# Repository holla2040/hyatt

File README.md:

# hyatt
A CNC wood router based on OpenBuilds WorkBee 1010, [Cypress PSoC 5LP CY8CKIT-059](http://www.cypress.com/documentation/development-kitsboards/cy8ckit-059-psoc-5lp-prototyping-kit-onboard-programmer-and) and [PSoC GRBL](https://github.com/bdring/Grbl_USB_Native). 

Hyatt Feature Set
* CY8KIT-059 based design
* 4 axis CNC controller, Dring GRBL port - PSoC HW pulse generation, debounce, interrupts
* Spindle speed/direction control - PSoC PWM
* Piezo element work piece probe - PSoC opamp, ADC, DAC comparator, interrupt
* Motor drive current monitor - PSoC analog mux and ADC
* Supply voltage monitor - PSoC ADC
* WiFi link with webserver, OTA, flash filesystem, websockets, TCP-serial bridge using ESP8266 - PSoC USART

Operator Interface
* 12 illuminated buttons via I2C I/O port expanders - PSoC I2C Fixed master
* Jog wheel with quad encoder - PSoC quad decoder
* 20x4 LCD panel display - PSoC I2C Fixed master
* 3.5" TFT 480x320 resistive touch screen display, attached to X axis gantry - PSoC USART
* Real-time feed speed override - PSoC ADC
* SDCard reader- PSoC SPI EmFile library
* Wireless CNC pendant - DirecTV remote control - my custom IR decoder using PSoC digital logic

[Hyatt Openbeam Workbee 1010 Settings](settings.txt)

PCB board, 100x100mm 2 layer, mixed through and smt parts

---

Getting boards from [JLCPCB](https://jlcpcb.com/), $2 for 10 boards + $18 DHL US shipping.

---

[Watch more hyatt videos](https://www.youtube.com/user/holla2040/search?query=hyatt)

---

Project named after Dale Hyatt, the one of the original K&F guitar amp cabinet makers. See "[The Sound Heard 'Round the World](https://www.halleonardbooks.com/product/viewproduct.action?itemid=332779 "Fender - The Sound Heard 'Round the World")", Richard Smith, p28.

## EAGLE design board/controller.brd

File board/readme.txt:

This information, board files, assembly instructions and bill of
materials are company confidental.
Not for distribution.

board
    hyatt

version
    1.0

date
    180804

fudicials at
    10,10
    96.88 

2 layer description
    2 layer board
        crc component cream
        plc component side silkscreen
        stc component side solder stop mask
        cmp component side copper
        sol solder side copper
        sts solder side solder stop mask
        pls solder side silkscreen
        crs solder cream

        drd drill data
        dri drill info
        gpi gerber info

2 layer stack up sequence
    top     x.cmp
    bottom  x.sol

contact info
    Craig Hollabaugh
    970 690 4911
    craig@hollabaugh.com

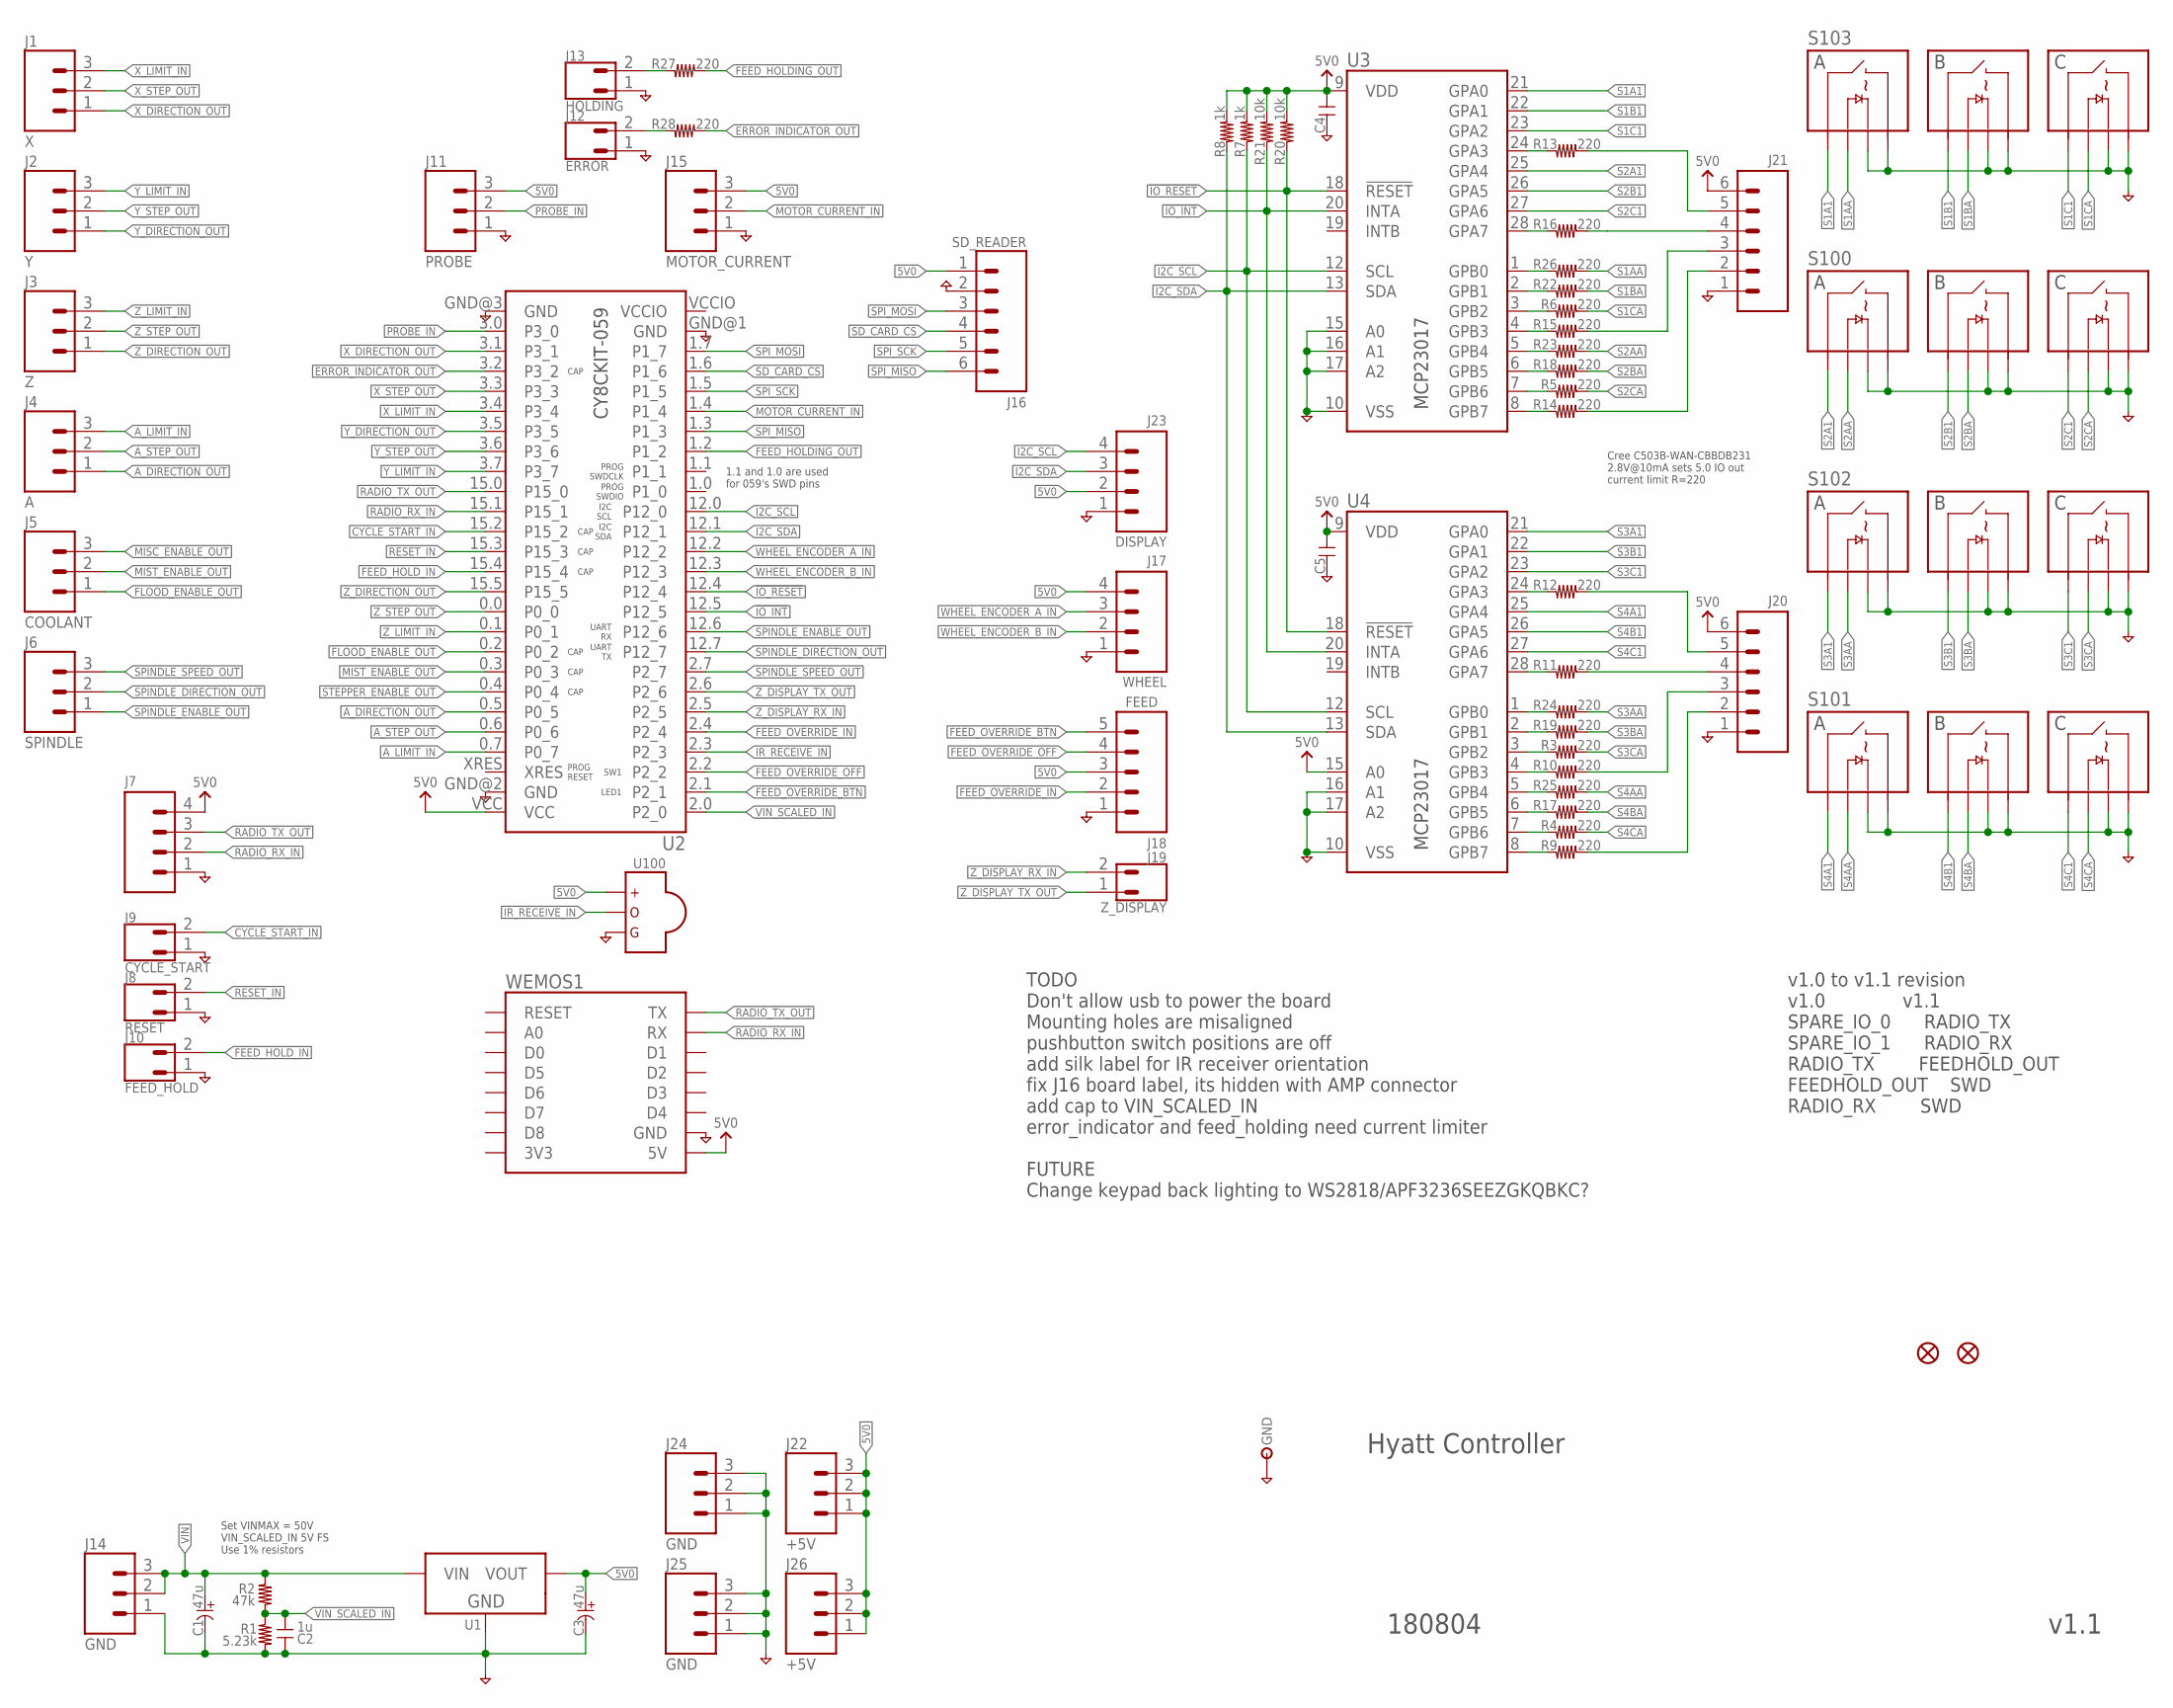
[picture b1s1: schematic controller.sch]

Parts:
C1, C3: 47u; E5-10
C2: 1u; C0603
C4, C5: C-0603; C0603
FID1, FID2: FIDUCIAL1.5X3; FIDUCIAL-1.5X3
GND: TESTPOINTTHRU; TPTHRU
J1: X; CONN-3.81MM-KF2EDG-3
J2: Y; CONN-3.81MM-KF2EDG-3
J3: Z; CONN-3.81MM-KF2EDG-3
J4: A; CONN-3.81MM-KF2EDG-3
J5: COOLANT; CONN-3.81MM-KF2EDG-3
J6: SPINDLE; CONN-3.81MM-KF2EDG-3
J7: CONN-04-0.1; 1X04
J8: RESET; CONN-.100-2
J9: CYCLE_START; CONN-.100-2
J10: FEED_HOLD; CONN-.100-2
J11: PROBE; CONN-3.81MM-KF2EDG-3
J12: ERROR; CONN-.100-2
J13: HOLDING; CONN-.100-2
J14, J24, J25: GND; CONN-3.81MM-KF2EDG-3
J15: MOTOR_CURRENT; CONN-3.81MM-KF2EDG-3
J16: SD_READER; 1X06
J17: WHEEL; CONN-.100-4
J18: FEED; 1X05
J19: Z_DISPLAY; CONN-3.81MM-KF2EDG-2
J20, J21: CONN-06-.100-VERT-HEADER; CONN-.100-6
J22, J26: +5V; CONN-3.81MM-KF2EDG-3
J23: DISPLAY; CONN-.100-4
R1: 5.23k; R0603
R2: 47k; R0603
R3, R4, R5, R6, R9, R10, R11, R12, R13, R14, R15, R16, R17, R18, R19, R22, R23, R24, R25, R26, R27, R28: 220; R0603
R7, R8: 1k; R0603
R20, R21: 10k; R0603
S100, S101, S102, S103: SWITCH-DTMF-3-LED
U1: VREG-SIP3
U2: BOARD-PSOC-CY8CKIT-059
U3, U4: MCP23017; SO28W
U100: SENSOR-IR-THRU; IRDETECTOR-THRU
WEMOS1: RADIO-WEMOS-D1-MINI; WEMOS-D1-MINI

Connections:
5V0: C3.+, C4.1, C5.1, J7.4, J11.3, J15.3, J16.1, J17.4, J18.3, J20.6, J21.6, J22.1, J22.2, J22.3, J23.2, J26.1, J26.2, J26.3, R7.2, R8.2, R20.2, R21.2, U1.3 (VOUT), U2.VCC, U3.9 (VDD), U4.9 (VDD), U4.15 (A0), U100.VCC, WEMOS1.5V
!IO_INT: R21.1, U2.12.5 (P12_5), U3.20 (INTA), U4.20 (INTA)
!IO_RESET: R20.1, U2.12.4 (P12_4), U3.18 (!RESET), U4.18 (!RESET)
A_DIRECTION_OUT: J4.1, U2.0.5 (P0_5)
A_LIMIT_IN: J4.3, U2.0.7 (P0_7)
A_STEP_OUT: J4.2, U2.0.6 (P0_6)
CYCLE_START_IN: J9.2, U2.15.2 (P15_2)
ERROR_INDICATOR_OUT: R28.2, U2.3.2 (P3_2)
FEED_HOLDING_OUT: R27.2, U2.1.2 (P1_2)
FEED_HOLD_IN: J10.2, U2.15.4 (P15_4)
FEED_OVERRIDE_BTN: J18.5, U2.2.1 (P2_1)
FEED_OVERRIDE_IN: J18.2, U2.2.4 (P2_4)
FEED_OVERRIDE_OFF: J18.4, U2.2.2 (P2_2)
FLOOD_ENABLE_OUT: J5.1, U2.0.2 (P0_2)
GND: C1.-, C2.2, C3.-, C4.2, C5.2, GND.1, J7.1, J8.1, J9.1, J10.1, J11.1, J12.1, J13.1, J14.1, J15.1, J16.2, J17.1, J18.1, J20.1, J21.1, J23.1, J24.1, J24.2, J24.3, J25.1, J25.2, J25.3, R1.1, S100.A_2, S100.A_C, S100.B_2, S100.B_C, S100.C_2, S100.C_C, S101.A_2, S101.A_C, S101.B_2, S101.B_C, S101.C_2, S101.C_C, S102.A_2, S102.A_C, S102.B_2, S102.B_C, S102.C_2, S102.C_C, S103.A_2, S103.A_C, S103.B_2, S103.B_C, S103.C_2, S103.C_C, U1.2 (GND), U2.GND@1 (GND), U2.GND@2 (GND), U2.GND@3 (GND), U3.10 (VSS), U3.15 (A0), U3.16 (A1), U3.17 (A2), U4.10 (VSS), U4.16 (A1), U4.17 (A2), U100.GND, WEMOS1.GND
I2C_SCL: J23.4, R7.1, U2.12.0 (P12_0), U3.12 (SCL), U4.12 (SCL)
I2C_SDA: J23.3, R8.1, U2.12.1 (P12_1), U3.13 (SDA), U4.13 (SDA)
IR_RECEIVE_IN: U2.2.3 (P2_3), U100.VOUT
MISC_ENABLE_OUT: J5.3
MIST_ENABLE_OUT: J5.2, U2.0.3 (P0_3)
MOTOR_CURRENT_IN: J15.2, U2.1.4 (P1_4)
unnamed: R26.1, U3.1 (GPB0)
unnamed: R22.1, U3.2 (GPB1)
unnamed: R13.1, U3.24 (GPA3)
unnamed: J21.5, R13.2
unnamed: R16.1, U3.28 (GPA7)
unnamed: J21.3, R15.2
unnamed: J21.4, R16.2
unnamed: R12.1, U4.24 (GPA3)
unnamed: R11.1, U4.28 (GPA7)
unnamed: J20.5, R12.2
unnamed: J20.4, R11.2
unnamed: J13.2, R27.1
unnamed: J12.2, R28.1
unnamed: R6.1, U3.3 (GPB2)
unnamed: R15.1, U3.4 (GPB3)
unnamed: R23.1, U3.5 (GPB4)
unnamed: R18.1, U3.6 (GPB5)
unnamed: R5.1, U3.7 (GPB6)
unnamed: R14.1, U3.8 (GPB7)
unnamed: R24.1, U4.1 (GPB0)
unnamed: R19.1, U4.2 (GPB1)
unnamed: R3.1, U4.3 (GPB2)
unnamed: R10.1, U4.4 (GPB3)
unnamed: R25.1, U4.5 (GPB4)
unnamed: R17.1, U4.6 (GPB5)
unnamed: R4.1, U4.7 (GPB6)
unnamed: R9.1, U4.8 (GPB7)
unnamed: J21.2, R14.2
unnamed: J20.3, R10.2
unnamed: J20.2, R9.2
PROBE_IN: J11.2, U2.3.0 (P3_0)
RADIO_RX_IN: J7.2, U2.15.1 (P15_1), WEMOS1.RX
RADIO_TX_OUT: J7.3, U2.15.0 (P15_0), WEMOS1.TX
RESET_IN: J8.2, U2.15.3 (P15_3)
S1A1: S103.A_1, U3.21 (GPA0)
S1AA: R26.2, S103.A_A
S1B1: S103.B_1, U3.22 (GPA1)
S1BA: R22.2, S103.B_A
S1C1: S103.C_1, U3.23 (GPA2)
S1CA: R6.2, S103.C_A
S2A1: S100.A_1, U3.25 (GPA4)
S2AA: R23.2, S100.A_A
S2B1: S100.B_1, U3.26 (GPA5)
S2BA: R18.2, S100.B_A
S2C1: S100.C_1, U3.27 (GPA6)
S2CA: R5.2, S100.C_A
S3A1: S102.A_1, U4.21 (GPA0)
S3AA: R24.2, S102.A_A
S3B1: S102.B_1, U4.22 (GPA1)
S3BA: R19.2, S102.B_A
S3C1: S102.C_1, U4.23 (GPA2)
S3CA: R3.2, S102.C_A
S4A1: S101.A_1, U4.25 (GPA4)
S4AA: R25.2, S101.A_A
S4B1: S101.B_1, U4.26 (GPA5)
S4BA: R17.2, S101.B_A
S4C1: S101.C_1, U4.27 (GPA6)
S4CA: R4.2, S101.C_A
SD_CARD_CS: J16.4, U2.1.6 (P1_6)
SPINDLE_DIRECTION_OUT: J6.2, U2.12.7 (P12_7)
SPINDLE_ENABLE_OUT: J6.1, U2.12.6 (P12_6)
SPINDLE_SPEED_OUT: J6.3, U2.2.7 (P2_7)
SPI_MISO: J16.6, U2.1.3 (P1_3)
SPI_MOSI: J16.3, U2.1.7 (P1_7)
SPI_SCK: J16.5, U2.1.5 (P1_5)
STEPPER_ENABLE_OUT: U2.0.4 (P0_4)
VIN: C1.+, J14.2, J14.3, R2.2, U1.1 (VIN)
VIN_SCALED_IN: C2.1, R1.2, R2.1, U2.2.0 (P2_0)
WHEEL_ENCODER_A_IN: J17.3, U2.12.2 (P12_2)
WHEEL_ENCODER_B_IN: J17.2, U2.12.3 (P12_3)
X_DIRECTION_OUT: J1.1, U2.3.1 (P3_1)
X_LIMIT_IN: J1.3, U2.3.4 (P3_4)
X_STEP_OUT: J1.2, U2.3.3 (P3_3)
Y_DIRECTION_OUT: J2.1, U2.3.5 (P3_5)
Y_LIMIT_IN: J2.3, U2.3.7 (P3_7)
Y_STEP_OUT: J2.2, U2.3.6 (P3_6)
Z_DIRECTION_OUT: J3.1, U2.15.5 (P15_5)
Z_DISPLAY_RX_IN: J19.2, U2.2.5 (P2_5)
Z_DISPLAY_TX_OUT: J19.1, U2.2.6 (P2_6)
Z_LIMIT_IN: J3.3, U2.0.1 (P0_1)
Z_STEP_OUT: J3.2, U2.0.0 (P0_0)

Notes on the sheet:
Hyatt Controller
180804
v1.1
TODO Don't allow usb to power the board Mounting holes are misaligned pushbutton switch positions are off add silk label for IR receiver orientation fix J16 board label, its hidden with AMP connector add cap to VIN_SCALED_IN error_indicator and feed_holding need current limiter FUTURE Change keypad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
Cree C503B-WAN-CBBDB231 2.8V@10mA sets 5.0 IO out current limit R=220
Set VINMAX = 50V VIN_SCALED_IN 5V FS Use 1% resistors
1.1 and 1.0 are used for 059's SWD pins
v1.0 to v1.1 revision v1.0 v1.1 SPARE_IO_0 RADIO_TX SPARE_IO_1 RADIO_RX RADIO_TX FEEDHOLD_OUT FEEDHOLD_OUT SWD RADIO_RX SWD

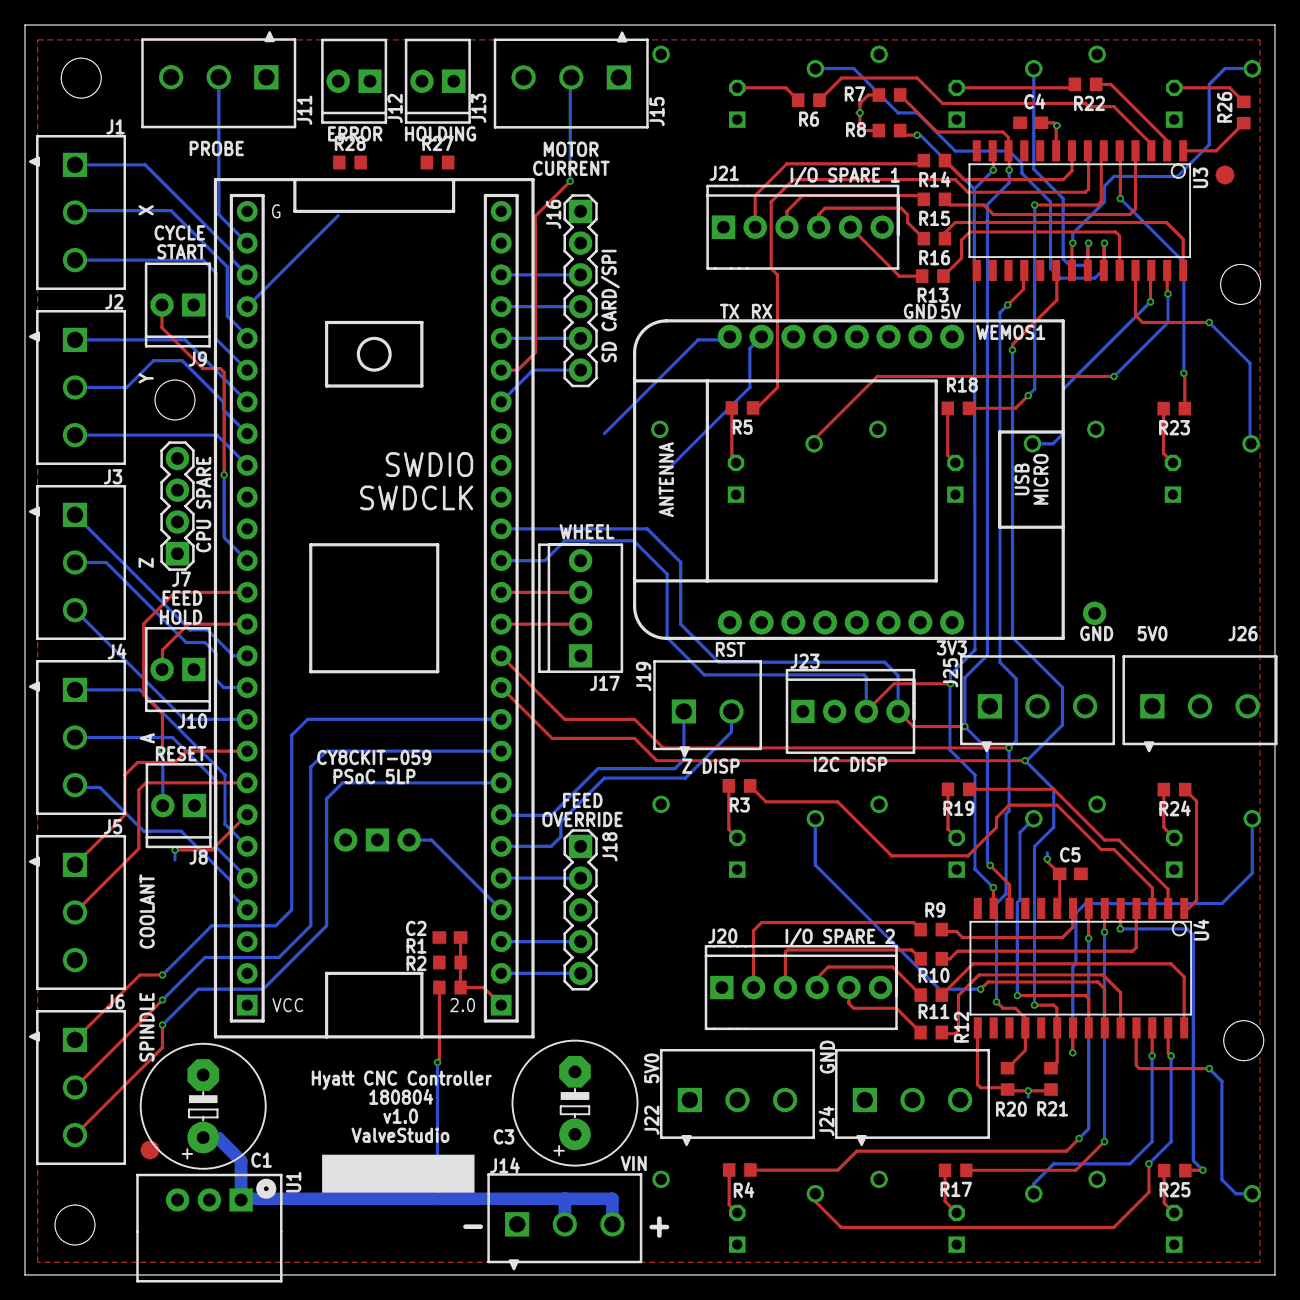
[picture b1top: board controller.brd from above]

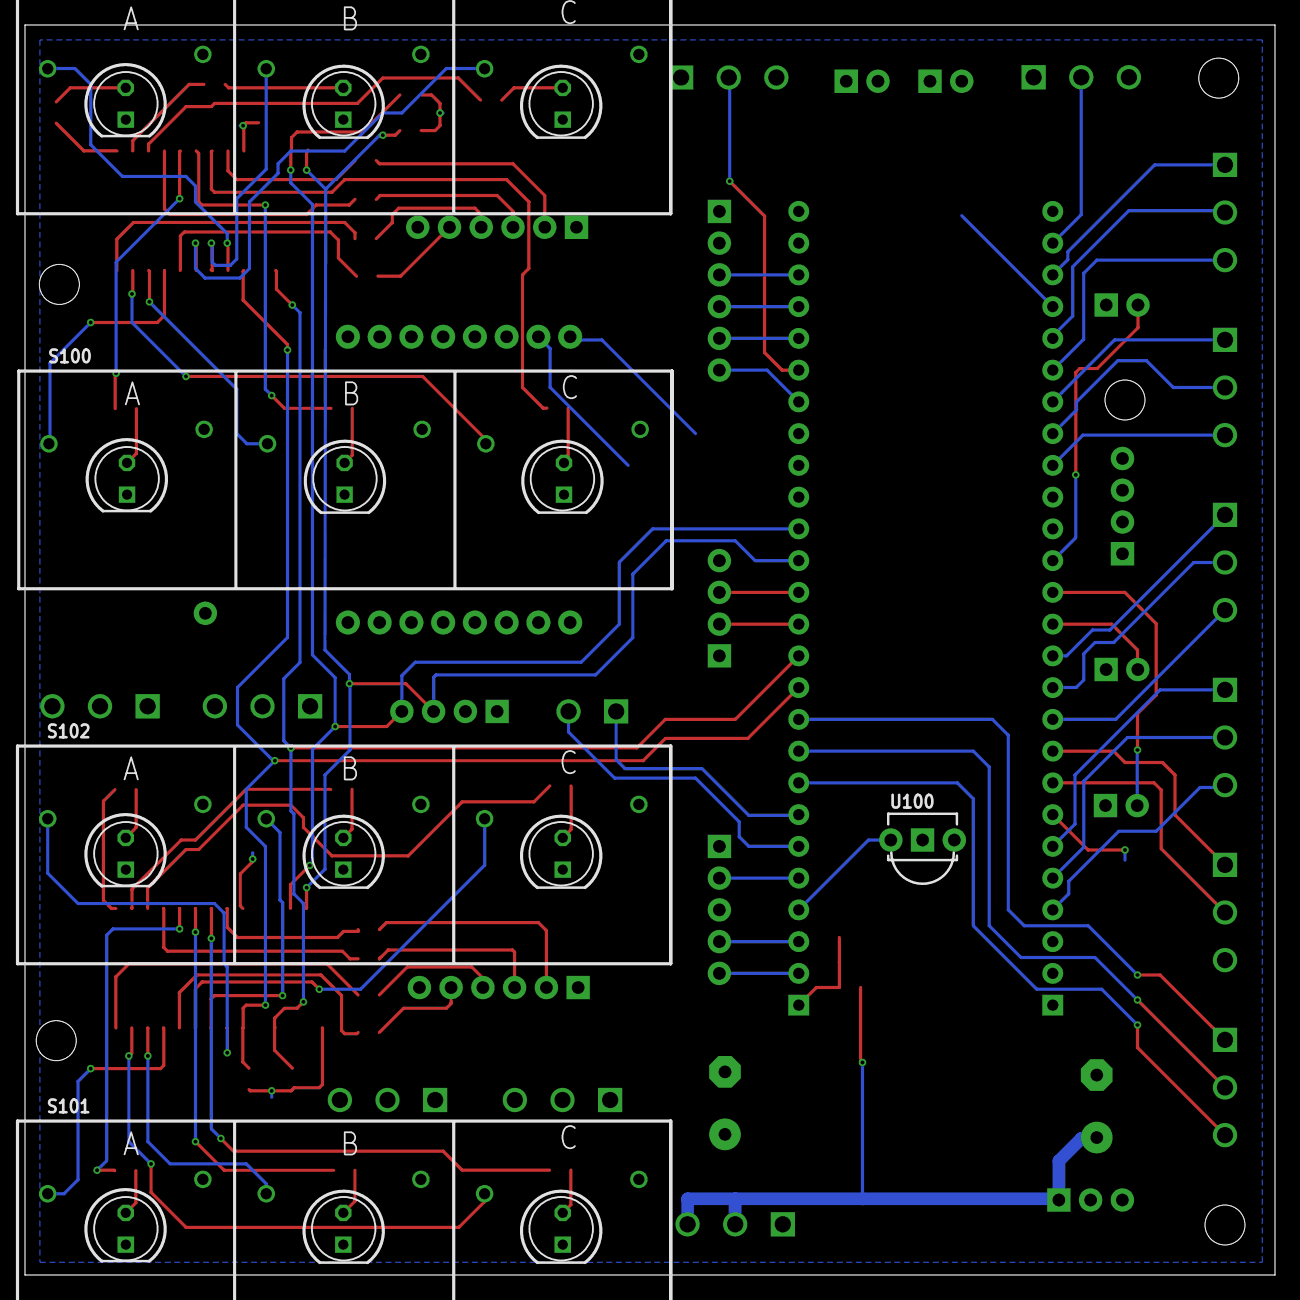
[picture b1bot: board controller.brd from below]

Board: 2 copper layers, 100.0 x 100.0 mm, 72 parts (5 on the bottom side), 100 nets.

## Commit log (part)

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2018-07-31 add dale hyatt image
2018-07-31 resized image
2018-07-31 fixing image
2018-07-31 readding dale hyatt
2018-07-31 initial add
2018-08-03 started routing added datasheets
2018-08-03 added datasheet continued routing
2018-08-03 pin assignment and routing near completion
2018-08-03 fixed 5V0/GND islands
2018-08-04 corrected keyboard switch dimensions
2018-08-04 initial add of files
2018-08-05 finished routing, almost ready to send
2018-08-06 re-organizing pin layout due to creator optimization
2018-08-06 reworked connector positions and pin mapping
2018-08-06 corrected wemos silkscreen
2018-08-06 fixed stepper_enable_out
2018-08-06 release v1.0
2018-08-06 removing readme with my name/phone
2018-08-06 initial add for design images
2018-08-06 corrected README lightened dale image
2018-08-07 initial add for board renders
2018-08-07 added workbee image
2018-08-08 fixed a couple issues and added creator's temp build files to ignore
2018-08-08 added 059 image
2018-08-08 update image
2018-08-17 updated wemos silk, added info to notes
2018-08-21 blinks 1A LED
2018-08-21 reading GPIOA, if S1A1 pressed, blinking pauses
2018-08-22 grouped the wires
2018-08-22 added component values to schematic cleaned up brd layout
2018-08-22 working on pushbutton interrupt
2018-08-24 now ignoring gerber files
2018-08-24 blinks both io expanders resets io expanders during initialization
2018-08-24 Update notes
2018-08-24 added keypad info
2018-08-24 added slow blink display
2018-08-24 now a better light show
2018-08-25 updated schematic info initial add for rest
2018-08-25 updated sch info added pushbutton datasheet
2018-08-26 updated some device line widths
2018-08-26 added serial reporting fixed binary counting to skip 0x08 'missing' bit u3 button indication now toggles per button press
2018-08-26 add trig functions and XYZ display
2018-08-26 uarts usb,wifi,display,kitprog all functional now
2018-08-26 a little cleaning in main.c started v1.1 of schematic, v1.0 boards need blue-wired
2018-08-27 updated several net names in schematic and psoc changed I2C to fixed instead of UDB
2018-08-28 enabled sdcard component and updated file include path
2018-08-31 updated a net name
2018-09-03 added terminal strip numberring
2018-09-03 don't know
2018-09-03 release dir org extracted release sch/brd files
    exacted
2018-09-03 inital add
2018-09-04 added interrupt driven x,y, and z display updates
2018-09-04 tweaked overlapping display areas
2018-09-05 now computing xyz continually and sending all the updates on a single line
2018-09-05 changed 96 to 80 point laid out buttons added override, status and feed fields status has 4 background colors, green, blue, yellow, red for grbl state line field now editable, added enter button to s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
2018-09-15 initial add for 2 datasheets updated routing drawing
2018-09-15 added jog wheel calcs
2018-09-16 updated a couple items
2018-09-17 started adding keypad
2018-09-17 file reorg now subdividing hyatt.c into components
2018-09-17 code reorg
2018-09-17 XYZ keys now work
2018-09-17 changed some define names
2018-09-18 updated key labels
2018-09-18 file re-org
2018-09-18 now have axisselect, jogwheelstepsize, unit, zero keys functioning
2018-09-18 added some ppcli notes
2018-09-19 added control panel display functionallity.
2018-09-19 added xyz to display
2018-09-19 have xyz kind of running changed to 3 axis
2018-09-19 working on offsets and report units for g20/g21
2018-09-20 now zeroing the selected axis correctly
2018-09-21 added spindle and air functionality now updating display during hold now reading usb during hold now sending init message on 'fake' usb dtr toggle to get ugs to 'see' reboot
2018-09-22 subbed in feedoverride now supports wheel operation added github gcode file
2018-09-22 feedover off position now holds/cyclestarts
2018-09-22 feedoverride now functional
2018-09-23 first submit on wifiBridge support
2018-09-23 tweaked display and keypad update rate to keep from starving planner keypad now disabled while not idle, except of mist
2018-09-23 tweaked display added select and sender
2018-09-23 sender functional
2018-09-24 back to longer xyz values, shifted all
2018-09-24 made the inch xyz display a char wider now setting feedoverride every 250ms
2018-09-25 added program and con targets
2018-09-27 started working on select
2018-09-27 added actions array added spindle on/off to github.nc
2018-09-27 file select and load functional
2018-09-27 showing showing file size
2018-09-27 now requires feed knob to be turned off in hold
2018-09-27 now action selection on override to off
2018-09-28 feedOverrideHandler now sends hold/cycle instead of loop
2018-09-28 improved keypad indicator display, indicator update had a 50mS delay added another error status_code to callback
2018-09-29 jog wheel improved doesn't override planning buffer sends jog commands out about 20 times faster, doesn't jump to run ~30mS after wheel stops turning, sends jog cancel
2018-10-02 added IR support
2018-10-03 added project feature set
2018-10-03 updating documentation
2018-10-04 added v1.0 to v1.1 notes
2018-10-04 probe functional
2018-10-04 added more documentation
2018-10-05 now routing spindle enable through estop, to keep AC out of controller box
2018-10-05 feedover now in increments of 10
2018-10-07 updated documentation
2018-10-07 changed status_control bit defines to match hardware
2018-10-08 added ZDisplay support
2018-10-09 fixed make issues
2018-10-11 cleaned up display started adding crc code
2018-10-12 working on file transfer over a websocket
2018-10-12 removed CR/LF
2018-10-13 starting re-org of ino file
2018-10-13 changed updated cad model
2018-10-13 added more fizes when when summer comes around
2018-10-21 another approach
2018-10-21 trying again
2018-10-22 funtional version
2018-10-22 now only working with display or keypad if they 'exist'
2018-10-22 small tweaks
2018-10-25 still hacking on thumps
2018-10-28 good working start hard and soft limits enable homing functional display refresh i2c is the issue with jogging
2018-10-29 just tweaking lcd ir pwr=$x prev=$h
2018-10-29 removed the lcd enable toggle delay increased LCD frame rate
2018-11-01 been hacking on z display code using bufferwrites
2018-11-01 added stateString function
2018-11-02 now lcd is using buffer writes
2018-11-02 tweaking display and keypad i2c bus sharing
2018-11-02 still tweaking on i2c
2018-11-02 added sprintf code back in, now functional
2018-11-02 still hacking on i2c sharing issues
2018-11-02 still hacking on i2c real machine, still hangs on the i2c restart for keypad reads
2018-11-02 simplified
2018-11-03 still i2c hacking
2018-11-03 changing interrupt configuration to interrupt-on-pin change, see 3.5.5 and 3.6.5
2018-11-03 change to interrupt-on-pin change successful. shorteded the wheel not change count to come out of jog faster
2018-11-03 now working on sender, moving to planner available flow control
2018-11-03 zdisplay functional mdi until back key functional feed > 9999 now 2c displays 9999 as feedrate
2018-11-03 sender uses now serial buffer count flow control, functional no longer using sender callback ir can cancel sender keypad holds off if display buffer is in progress
2018-11-04 wheel now uses serial buffer avail for flow control x and y move at same time during homing
2018-11-05 making a lot changes to find the serial ring buffer issue
2018-11-22 added info on laser driver board
2018-11-25 changed to inches, removed flange opening, now for 23/64" flush inserts
2018-11-28 added md
2018-11-28 added additional items
2019-03-03 don't know what changes are
2019-03-03 trying to get spind_enable signal functional
2019-03-03 fixed the inversion problem with spindle keypad backlight
2019-03-03 tweaking spindle_enable_out code
2019-03-03 mist, flood and spindle control now functional
2019-03-06 added currect limit resistors for holding and error control panel leds added alarm string to control panel display if in alarm state, hitting any control panel key clears alarm without reseting
2019-03-06 now calling hyattLoop if hard limit causes error at startup
2019-03-06 now calling hyattLoop during homing per axis
2019-03-06 added a fake initial z position to move off work piece after power cycle
2019-03-06 disabled soft limit check for jogs
2019-03-06 loading lastBlock in display init to message user about homing required
2019-03-07 updated remote button definitions, added some new items
2019-03-07 reworked MDI to exist on idle screen
2019-03-07 mdi re-work functional
2019-03-07 now calling hyattLoop more times during homing
2019-03-11 tracking down soft limit error
2019-03-11 hacking on sender flow control
2019-03-11 still hacking on sender
2019-03-11 sender hacking
2019-03-11 sender more reliable now
2019-03-11 sender cleanup added fusion360 hyatt post processor
2019-03-11 changed play to run 1001.nc
2019-03-12 updated settings
2019-03-12 added define for insert hole nc
2019-03-17 updated steps/mm
2019-03-17 added a note
2019-03-18 key 2,3 is now the 'enter', not the coord select started working on G92 offset using laser crosshair got the config #33 and #34 config to save, recall and report
2019-03-19 refactored action to macro
2019-03-19 started work on inspect functionality
2019-03-20 initial add for cmm functionality
2019-03-21 added first pass at inspect keypad definition for lower 2 rows initial add for g code analyzer
2019-04-14 now soft-reset will also calls hyattinit and will stop the sender
2019-04-14 sch added a couple values so charm.ulp would place ICs
    makefile
    moved so vim's ctrl-m would make project
    src
    not using G92 anymore, just setting selected coordinate system using hyatt_zero_offset_x,y from grbl settings #33 and #34
2019-04-14 hyatt_zero_offset_x,y now functional
2019-06-05 bounding box added
2019-06-05 adding missing files
2019-06-06 added runOp function
2019-06-06 major version dev work, broken, do not use
2019-06-06 refactored sender to file
2019-06-06 finished file refactor, this is not tested
2019-06-07 working on file perimeter
2019-06-07 added file perim message, added NE,SW blocksend
2019-06-07 taking inspect out select loop for now
2019-06-07 still hacking on file ops
2019-06-07 file hacking
2019-06-07 file hacking perimeter scanning happens on file select
2019-06-07 file ops hacking
2019-06-07 fixed operation scanner for display
2019-06-08 file operation hacking
2019-06-08 op -, op 1, op + implemented but not tested
2019-06-08 op hacking
2019-06-09 fixed fileSize issue
2019-06-09 file ops hacking, added header op
2019-06-09 file send hacking, added header op
2019-06-09 tweaking ui
2019-06-09 updated x0y0 macro
2019-06-09 added more model display to Z now z wheel can't select fast
2019-06-09 corrected cheatsheet, updated todo
2019-06-09 hacking on header send fails
2019-06-09 trying to fix wheel0 restore on single op select and sender holding reset
2019-06-09 added homing on reboot
2019-06-09 file ops wheel0Select
2019-06-09 fixed wheel0Select zero issue g28 macro now goes up before xy move
2019-06-09 updaing the z display layout
2019-06-10 added commentable code for updating the nextion display
2019-06-10 added NEXTION define for zdisplay flashing updated zdisplay info lines
2019-06-10 fixed the single last op fail
2019-06-10 fixed the screen update on op ending
2019-06-10 working on hard limit toggling to move axis if hard limit event occurred
2019-06-10 added delay to see hard limit setting after toggle
2019-06-10 added hardware limit setting display at startup
2019-06-10 added inspect specifics
2019-06-12 added tool center X0 Y0 macro
2019-06-12 added 2 macros
2019-06-17 axis zero now only works in control panel idle IR advance key does G30
2019-06-29 updated ir drawing initial add for surfaceGen.py
2019-06-29 NW,SE,etc now sending G90
2019-07-04 started adding in hyatt functions
2019-07-04 function labels now copied in setup
2019-07-04 updated a macro
2019-07-04 updating macros
2019-07-04 updated macros
2019-07-04 working on function calling and laser crossair offset
2019-07-04 fixed laser x0 y0 set
2019-07-04 started work on inspect
2019-07-05 working on inspect
2019-07-05 inspect work
2019-07-05 worked on surfaceGen.py
2019-07-05 added M50 feed hold
2019-09-08 added linux build instructions
